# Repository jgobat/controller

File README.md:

# controller

Main control board for simple buoyancy driven underwater vehicles. Based around Teensy 3.6.

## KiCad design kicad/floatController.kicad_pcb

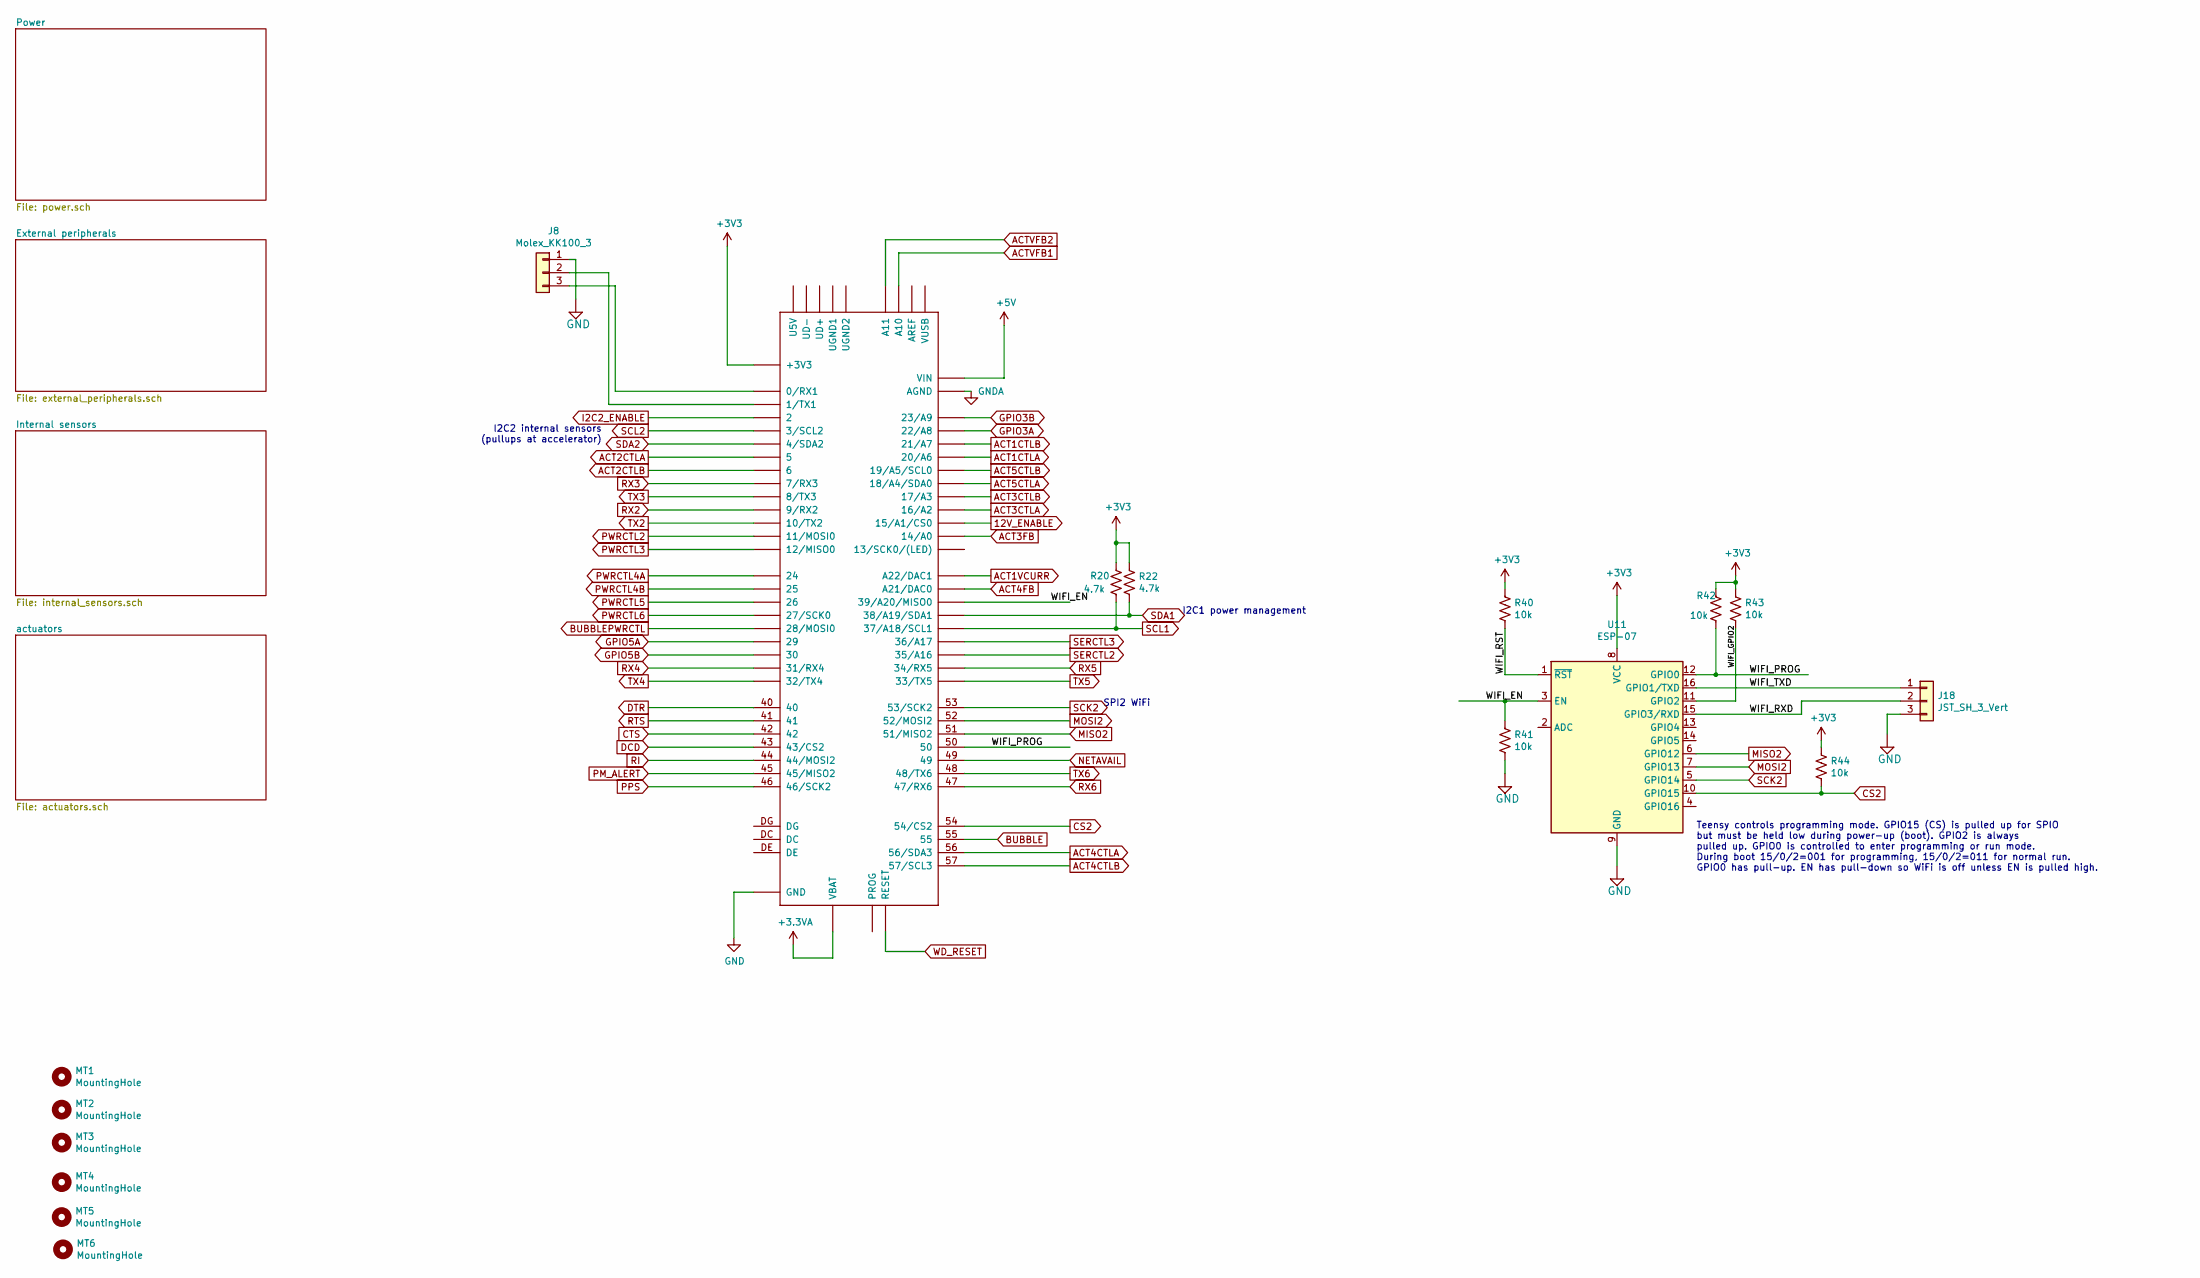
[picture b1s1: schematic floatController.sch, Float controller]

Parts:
J8: Molex_KK100_3; Molex_KK-254_AE-6410-03A_1x03_P2.54mm_Vertical; Manufacturer pn 0022235031; Digikey WM13451-ND
J18: JST_SH_3_Vert; JST_SH_BM03B-SRSS-TB_1x03-1MP_P1.00mm_Vertical; Manufacturer pn BM03B-SRSS-TB(LF)(SN); Digikey 455-1789-1-ND
MT1, MT2, MT3, MT4: MountingHole; MountingHole_3mm_Pad
MT5, MT6: MountingHole; MountingHole_2.5mm
R20, R22: 4.7k; R_0603_1608Metric_Pad1.05x0.95mm_HandSolder; Rating 5%, 1/10W; Manufacturer pn ERJ-3GEYJ472V; Digikey P4.7KGCT-ND
R40, R41, R42, R43, R44: 10k; R_0603_1608Metric_Pad1.05x0.95mm_HandSolder; Manufacturer pn ERJ-3GEYJ103V; Digikey P10KGCT-ND
U1: TEENSY_3.5_3.6; Digikey 1568-1442-ND
U11: ESP-07; Manufacturer pn ESP-07S; Digikey ESP-07S-ND

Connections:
12V_ENABLE: U1.15 (15/A1/CS0); also elsewhere on the board
+3.3VA: U1.VBAT; also elsewhere on the board
+3V3: R20.1, R22.1, R40.1, R42.1, R43.1, R44.1, U1.3V3 (+3V3), U1.3V3_2, U1.3V3_3, U1.3V3_LO, U11.8 (VCC); also elsewhere on the board
+5V: U1.VIN; also elsewhere on the board
/WIFI_EN: R41.1, U1.39 (39/A20/MISO0), U11.3 (EN)
/WIFI_GPIO2: R43.2, U11.11 (GPIO2)
/WIFI_PROG: R42.2, U1.50, U11.12 (GPIO0)
/WIFI_RST: R40.2, U11.1 (~RST)
/WIFI_RXD: J18.2, U11.15 (GPIO3/RXD)
/WIFI_TXD: J18.1, U11.16 (GPIO1/TXD)
ACT1CTLA: U1.20 (20/A6); also elsewhere on the board
ACT1CTLB: U1.21 (21/A7); also elsewhere on the board
ACT1VCURR: U1.A22 (A22/DAC1); also elsewhere on the board
ACT2CTLA: U1.5; also elsewhere on the board
ACT2CTLB: U1.6; also elsewhere on the board
ACT3CTLA: U1.16 (16/A2); also elsewhere on the board
ACT3CTLB: U1.17 (17/A3); also elsewhere on the board
ACT3FB: U1.14 (14/A0); also elsewhere on the board
ACT4CTLA: U1.56 (56/SDA3); also elsewhere on the board
ACT4CTLB: U1.57 (57/SCL3); also elsewhere on the board
ACT4FB: U1.A21 (A21/DAC0); also elsewhere on the board
ACT5CTLA: U1.18 (18/A4/SDA0); also elsewhere on the board
ACT5CTLB: U1.19 (19/A5/SCL0); also elsewhere on the board
ACTVFB1: U1.A10; also elsewhere on the board
ACTVFB2: U1.A11; also elsewhere on the board
BUBBLE: U1.55; also elsewhere on the board
BUBBLEPWRCTL: U1.28 (28/MOSI0); also elsewhere on the board
CS2: R44.2, U1.54 (54/CS2), U11.10 (GPIO15)
CTS: U1.42; also elsewhere on the board
DCD: U1.43 (43/CS2); also elsewhere on the board
DTR: U1.40; also elsewhere on the board
GND: J8.1, J18.3, R41.2, U1.GND, U1.GND2, U1.GND3, U1.GND4, U1.GND5, U11.9 (GND); also elsewhere on the board
GNDA: U1.AGND; also elsewhere on the board
GPIO3A: U1.22 (22/A8); also elsewhere on the board
GPIO3B: U1.23 (23/A9); also elsewhere on the board
GPIO5A: U1.29; also elsewhere on the board
GPIO5B: U1.30; also elsewhere on the board
I2C2_ENABLE: U1.2; also elsewhere on the board
MISO2: U1.51 (51/MISO2), U11.6 (GPIO12)
MOSI2: U1.52 (52/MOSI2), U11.7 (GPIO13)
NETAVAIL: U1.49; also elsewhere on the board
unnamed: J8.2, U1.1 (1/TX1)
unnamed: J8.3, U1.0 (0/RX1)
PM_ALERT: U1.45 (45/MISO2); also elsewhere on the board
PPS: U1.46 (46/SCK2); also elsewhere on the board
PWRCTL2: U1.11 (11/MOSI0); also elsewhere on the board
PWRCTL3: U1.12 (12/MISO0); also elsewhere on the board
PWRCTL4A: U1.24; also elsewhere on the board
PWRCTL4B: U1.25; also elsewhere on the board
PWRCTL5: U1.26; also elsewhere on the board
PWRCTL6: U1.27 (27/SCK0); also elsewhere on the board
RI: U1.44 (44/MOSI2); also elsewhere on the board
RTS: U1.41; also elsewhere on the board
RX2: U1.9 (9/RX2); also elsewhere on the board
RX3: U1.7 (7/RX3); also elsewhere on the board
RX4: U1.31 (31/RX4); also elsewhere on the board
RX5: U1.34 (34/RX5); also elsewhere on the board
RX6: U1.47 (47/RX6); also elsewhere on the board
SCK2: U1.53 (53/SCK2), U11.5 (GPIO14)
SCL1: R20.2, U1.37 (37/A18/SCL1); also elsewhere on the board
SCL2: U1.3 (3/SCL2); also elsewhere on the board
SDA1: R22.2, U1.38 (38/A19/SDA1); also elsewhere on the board
SDA2: U1.4 (4/SDA2); also elsewhere on the board
SERCTL2: U1.35 (35/A16); also elsewhere on the board
SERCTL3: U1.36 (36/A17); also elsewhere on the board
TX2: U1.10 (10/TX2); also elsewhere on the board
TX3: U1.8 (8/TX3); also elsewhere on the board
TX4: U1.32 (32/TX4); also elsewhere on the board
TX5: U1.33 (33/TX5); also elsewhere on the board
TX6: U1.48 (48/TX6); also elsewhere on the board
WD_RESET: U1.RESET; also elsewhere on the board

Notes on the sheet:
I2C1 power management
I2C2 internal sensors (pullups at accelerator)
SPI2 WiFi
Teensy controls programming mode. GPIO15 (CS) is pulled up for SPIO but must be held low during power-up (boot). GPIO2 is always pulled up. GPIO0 is controlled to enter programming or run mode. During boot 15/0/2=001 for programming, 15/0/2=011 for normal run. GPIO0 has pull-up. EN has pull-down so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

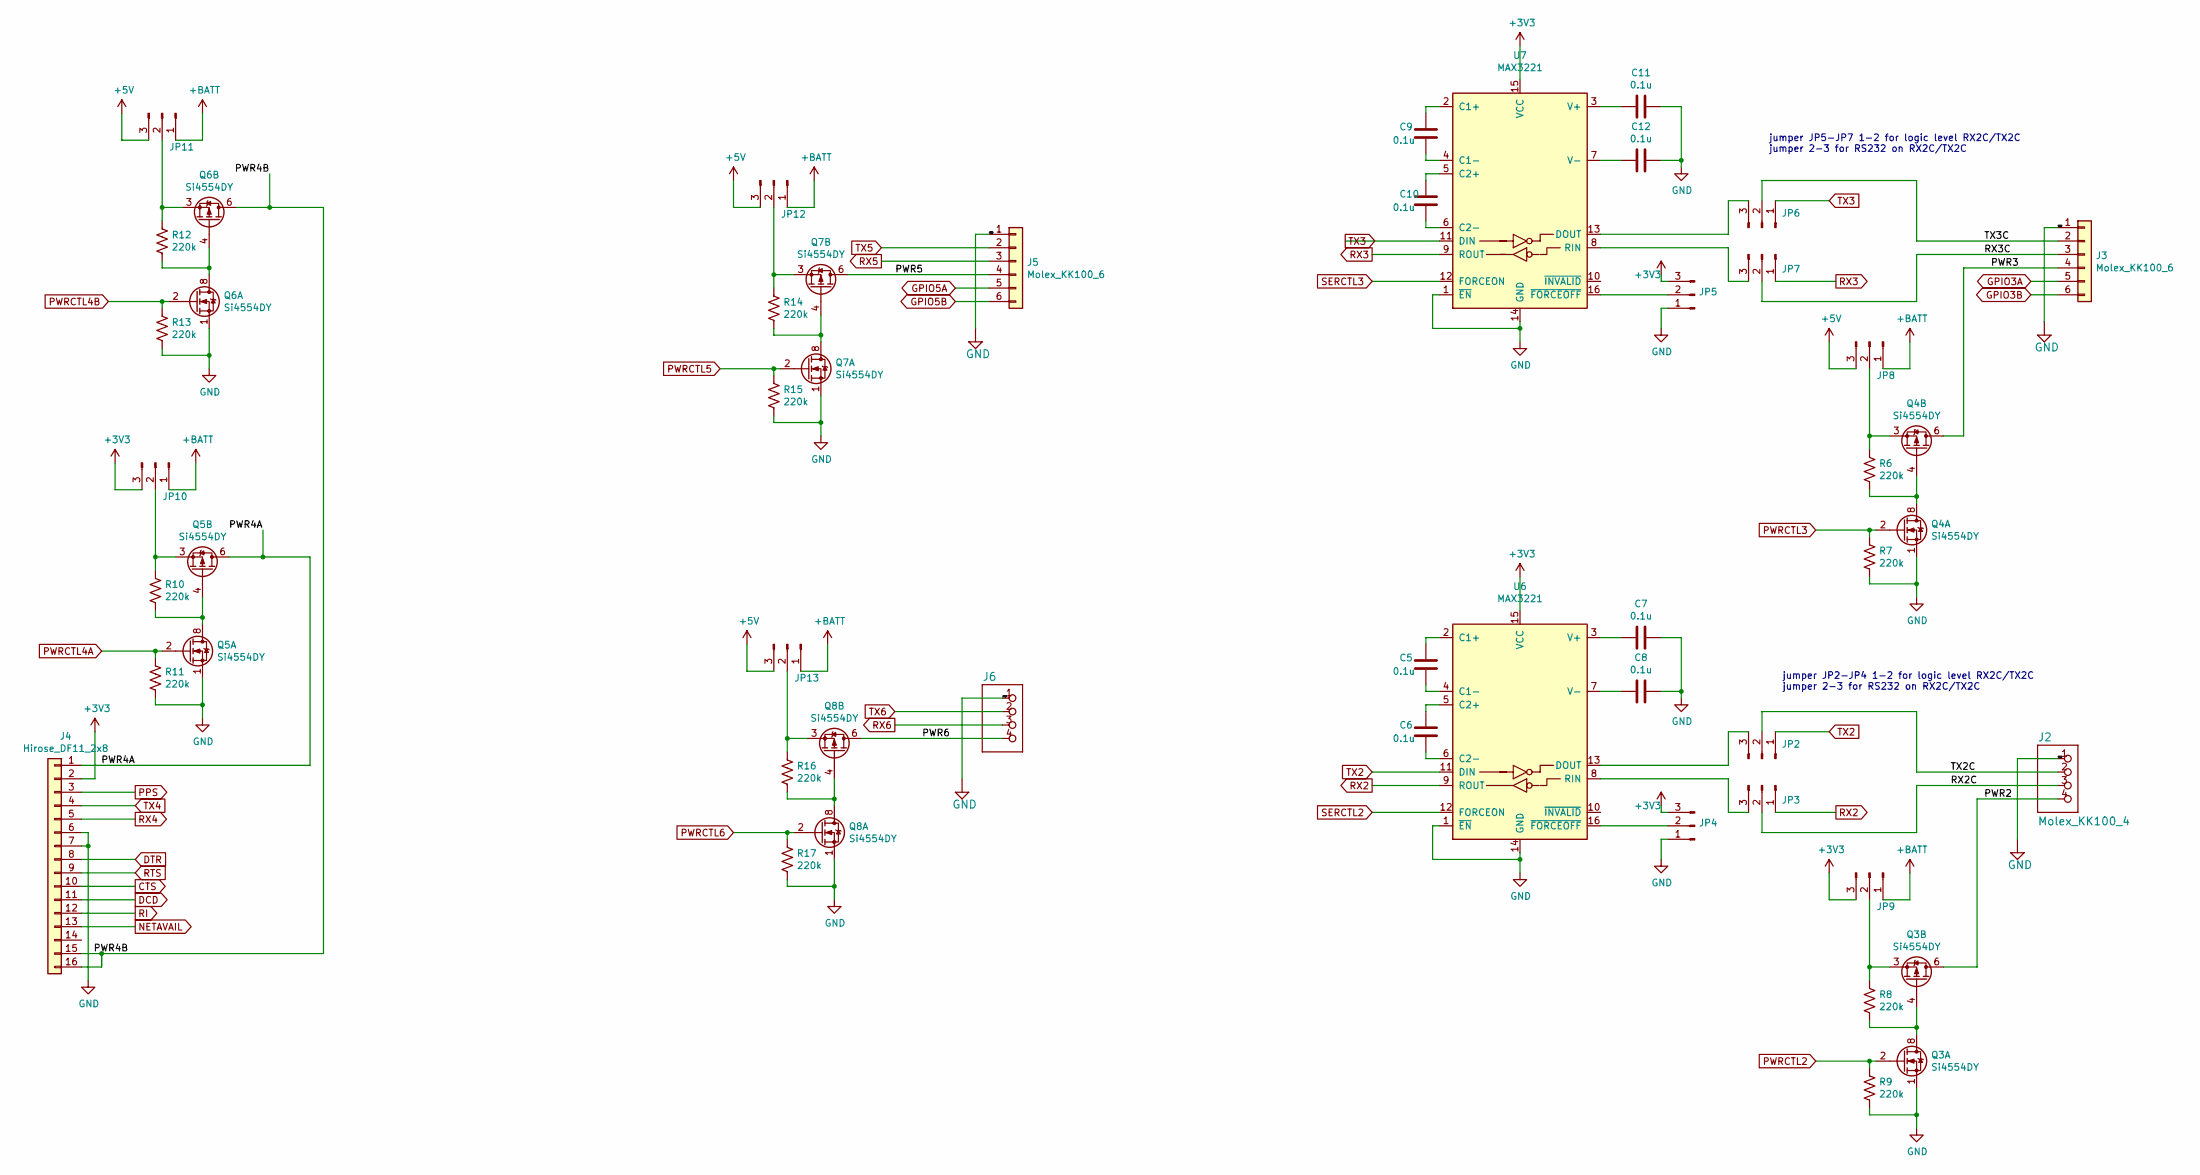
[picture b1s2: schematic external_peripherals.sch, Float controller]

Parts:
C5, C6, C7, C8, C9, C10, C11, C12: 0.1u; C_0603_1608Metric_Pad1.05x0.95mm_HandSolder; Manufacturer pn GCJ188R71E104KA12D‎; Digikey 490-16477-1-ND
J2, J6: Molex_KK100_4; Molex_KK-254_AE-6410-04A_1x04_P2.54mm_Vertical; Manufacturer pn 0022232041; Digikey WM4202-ND
J3, J5: Molex_KK100_6; Molex_KK-254_AE-6410-06A_1x06_P2.54mm_Vertical; Manufacturer pn 0022232061; Digikey WM4204-ND
J4: Hirose_DF11_2x8; Hirose_DF11-16DP-2DSA_2x08_P2.00mm_Vertical; Manufacturer pn DF11-16DP-2DSA(01); Digikey H2856-ND
JP2, JP3, JP4, JP5, JP6, JP7, JP8, JP9, JP12, JP13: PinHead_2.54mm_3; PinHeader_1x03_P2.54mm_Vertical
JP10: 0.003 0603; R0603_3position_jumper; Digikey 738-CSS0603FT3L00CT-ND
JP11: 0.003 0603; R0603_3position_jumper
Q3, Q4, Q5, Q6, Q7, Q8: Si4554DY; SOIC-8_3.9x4.9mm_P1.27mm; Manufacturer pn SI4554DY-T1-GE3; Digikey SI4554DY-T1-GE3CT-ND
R6, R7, R8, R9, R10, R11, R12, R13, R14, R15, R16, R17: 220k; R_0603_1608Metric_Pad1.05x0.95mm_HandSolder; Rating 5%, 1/10W; Manufacturer pn ERJ-3GEYJ224V; Digikey P220KGCT-ND
U6, U7: MAX3221; SSOP-16_5.3x6.2mm_P0.65mm; Manufacturer pn MAX3221IDBR; Digikey 296-9595-1-ND

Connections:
+3V3: J4.2, JP4.3, JP5.3, JP9.3, JP10.3, U6.15 (VCC), U7.15 (VCC); also elsewhere on the board
+5V: JP8.3, JP11.3, JP12.3, JP13.3; also elsewhere on the board
+BATT: JP8.1, JP9.1, JP10.1, JP11.1, JP12.1, JP13.1; also elsewhere on the board
/External peripherals/PWR2: J2.4, Q3.5 (D), Q3.6 (D)
/External peripherals/PWR3: J3.4, Q4.5 (D), Q4.6 (D)
/External peripherals/PWR4A: J4.1, Q5.5 (D), Q5.6 (D)
/External peripherals/PWR4B: J4.15, J4.16, Q6.5 (D), Q6.6 (D)
/External peripherals/PWR5: J5.4, Q7.5 (D), Q7.6 (D)
/External peripherals/PWR6: J6.4, Q8.5 (D), Q8.6 (D)
/External peripherals/RX2C: J2.3, JP3.2
/External peripherals/RX3C: J3.3, JP7.2
/External peripherals/TX2C: J2.2, JP2.2
/External peripherals/TX3C: J3.2, JP6.2
CTS: J4.10; also elsewhere on the board
DCD: J4.11; also elsewhere on the board
DTR: J4.8; also elsewhere on the board
GND: C7.1, C8.1, C11.1, C12.1, J2.1, J3.1, J4.6, J4.7, J5.1, J6.1, JP4.1, JP5.1, Q3.1 (S), Q4.1 (S), Q5.1 (S), Q6.1 (S), Q7.1 (S), Q8.1 (S), R7.2, R9.2, R11.2, R13.2, R15.2, R17.2, U6.1 (~EN), U6.14 (GND), U7.1 (~EN), U7.14 (GND); also elsewhere on the board
GPIO3A: J3.5; also elsewhere on the board
GPIO3B: J3.6; also elsewhere on the board
GPIO5A: J5.5; also elsewhere on the board
GPIO5B: J5.6; also elsewhere on the board
NETAVAIL: J4.13; also elsewhere on the board
unnamed: C5.1, U6.2 (C1+)
unnamed: C5.2, U6.4 (C1-)
unnamed: C6.1, U6.5 (C2+)
unnamed: C6.2, U6.6 (C2-)
unnamed: C7.2, U6.3 (V+)
unnamed: C8.2, U6.7 (V-)
unnamed: C9.1, U7.2 (C1+)
unnamed: C9.2, U7.4 (C1-)
unnamed: C10.1, U7.5 (C2+)
unnamed: C10.2, U7.6 (C2-)
unnamed: C11.2, U7.3 (V+)
unnamed: C12.2, U7.7 (V-)
unnamed: JP2.3, U6.13 (DOUT)
unnamed: JP3.3, U6.8 (RIN)
unnamed: JP4.2, U6.16 (~FORCEOFF)
unnamed: JP5.2, U7.16 (~FORCEOFF)
unnamed: JP6.3, U7.13 (DOUT)
unnamed: JP7.3, U7.8 (RIN)
unnamed: JP8.2, Q4.3 (1), R6.1
unnamed: JP9.2, Q3.3 (1), R8.1
unnamed: JP10.2, Q5.3 (1), R10.1
unnamed: JP11.2, Q6.3 (1), R12.1
unnamed: JP12.2, Q7.3 (1), R14.1
unnamed: JP13.2, Q8.3 (1), R16.1
unnamed: Q3.4 (G), Q3.7 (D), Q3.8 (D), R8.2
unnamed: Q4.4 (G), Q4.7 (D), Q4.8 (D), R6.2
unnamed: Q5.4 (G), Q5.7 (D), Q5.8 (D), R10.2
unnamed: Q6.4 (G), Q6.7 (D), Q6.8 (D), R12.2
unnamed: Q7.4 (G), Q7.7 (D), Q7.8 (D), R14.2
unnamed: Q8.4 (G), Q8.7 (D), Q8.8 (D), R16.2
PPS: J4.3; also elsewhere on the board
PWRCTL2: Q3.2 (G), R9.1; also elsewhere on the board
PWRCTL3: Q4.2 (G), R7.1; also elsewhere on the board
PWRCTL4A: Q5.2 (G), R11.1; also elsewhere on the board
PWRCTL4B: Q6.2 (G), R13.1; also elsewhere on the board
PWRCTL5: Q7.2 (G), R15.1; also elsewhere on the board
PWRCTL6: Q8.2 (G), R17.1; also elsewhere on the board
RI: J4.12; also elsewhere on the board
RTS: J4.9; also elsewhere on the board
RX2: JP3.1, U6.9 (ROUT); also elsewhere on the board
RX3: JP7.1, U7.9 (ROUT); also elsewhere on the board
RX4: J4.5; also elsewhere on the board
RX5: J5.3; also elsewhere on the board
RX6: J6.3; also elsewhere on the board
SERCTL2: U6.12 (FORCEON); also elsewhere on the board
SERCTL3: U7.12 (FORCEON); also elsewhere on the board
TX2: JP2.1, U6.11 (DIN); also elsewhere on the board
TX3: JP6.1, U7.11 (DIN); also elsewhere on the board
TX4: J4.4; also elsewhere on the board
TX5: J5.2; also elsewhere on the board
TX6: J6.2; also elsewhere on the board

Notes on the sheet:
jumper JP5-JP7 1-2 for logic level RX2C/TX2C jumper 2-3 for RS232 on RX2C/TX2C
jumper JP2-JP4 1-2 for logic level RX2C/TX2C jumper 2-3 for RS232 on RX2C/TX2C

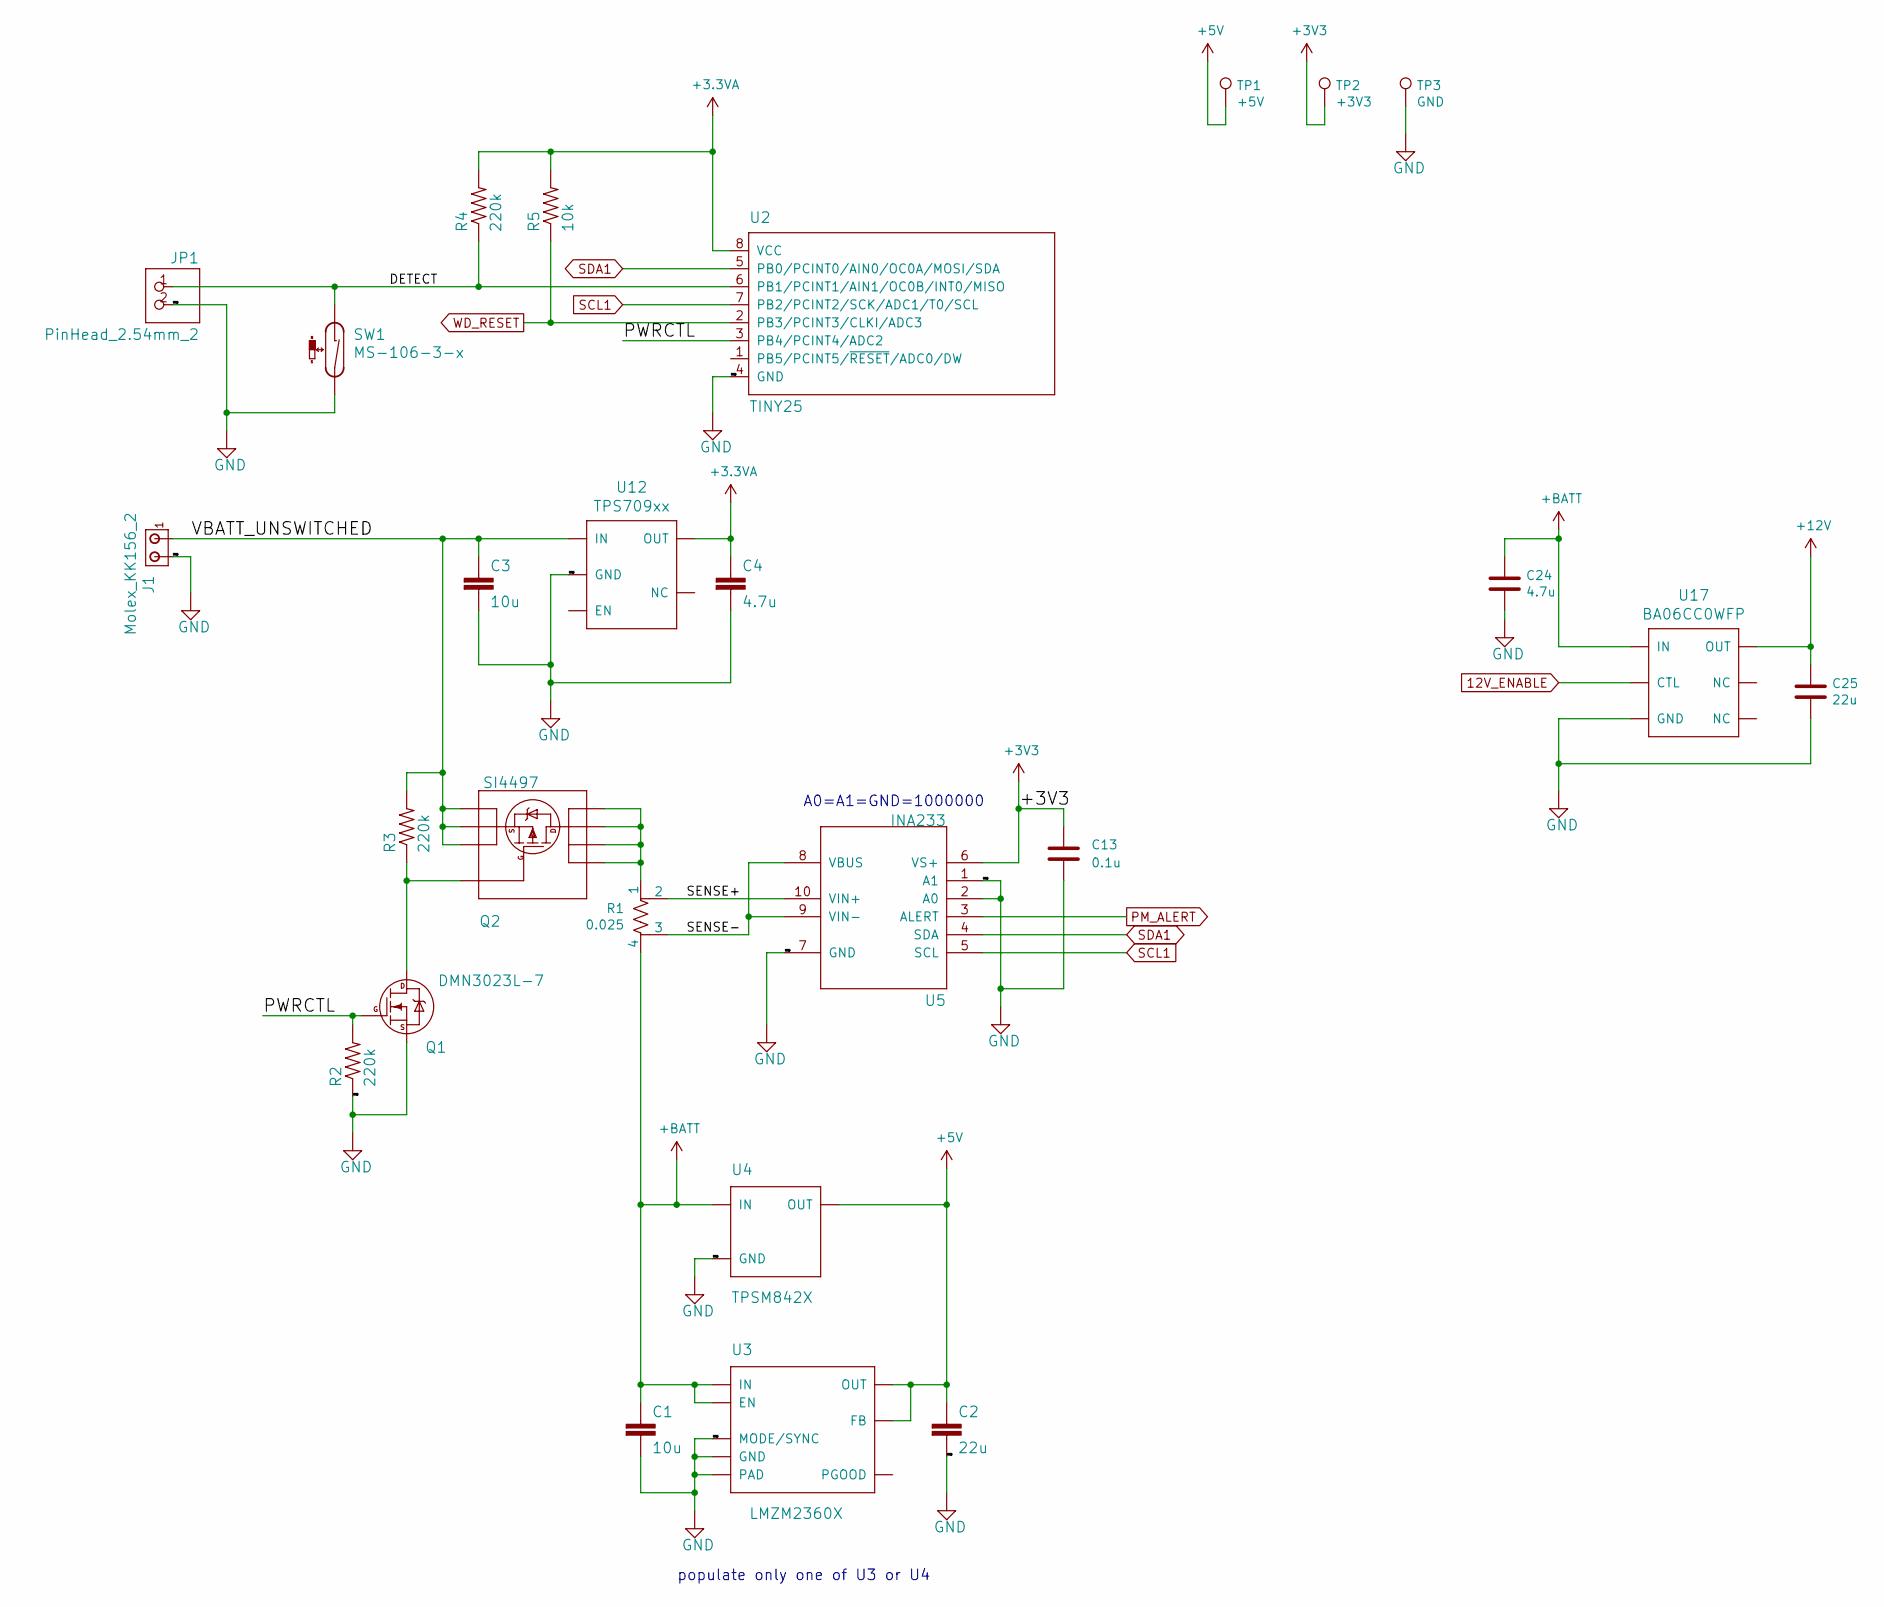
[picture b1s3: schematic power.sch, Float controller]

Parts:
C1: 10u; C_1206_3216Metric_Pad1.42x1.75mm_HandSolder; Rating 7.3u effective at 15V; Manufacturer pn ‎GCM32ER71E106KA57L‎; Digikey 490-4798-1-ND‎
C2: 22u; C_1206_3216Metric_Pad1.42x1.75mm_HandSolder; Rating 20u effective at 5V; Manufacturer pn ‎GCM32ER71A226KE12L‎; Digikey 490-4797-1-ND‎
C3: 10u; C_0805_2012Metric_Pad1.15x1.40mm_HandSolder; Rating 2.2u at 15V; Manufacturer pn GRM21BR6YA106KE43L‎; Digikey 490-10514-1-ND‎
C4: 4.7u; C_0603_1608Metric_Pad1.05x0.95mm_HandSolder; Rating 2.3u at 3.3V (min 1.5u for Vout > 1.5V); Manufacturer pn ‎GRM185R61C475ME11D; Digikey 490-16347-1-ND
C13: 0.1u; C_0603_1608Metric_Pad1.05x0.95mm_HandSolder; Manufacturer pn GCJ188R71E104KA12D‎; Digikey 490-16477-1-ND
C24: 4.7u; C_1206_3216Metric_Pad1.42x1.75mm_HandSolder; Rating 50V
C25: 22u; C_1210_3225Metric_Pad1.42x2.65mm_HandSolder; Rating 25V
J1: Molex_KK156_2; Molex_KK-396_A-41791-0002_1x02_P3.96mm_Vertical; Manufacturer pn ‎0009652028‎; Digikey WM18823-ND
JP1: PinHead_2.54mm_2; PinHeader_1x02_P2.54mm_Vertical
Q1: DMN3023L-7; SOT-23; Manufacturer pn DMN3023L-7; Digikey DMN3023L-7DICT-ND
Q2: SI4497; SOIC-8_3.9x4.9mm_P1.27mm; Manufacturer pn SI4497DY-T1-GE3; Digikey SI4497DY-T1-GE3CT-ND
R1: 0.025; R_Shunt_Ohmite_LVK24; Rating 0.5%, 1W (6A); Manufacturer pn LVK24R025DER; Digikey LVK24R025DERCT-ND
R2, R3, R4: 220k; R_0603_1608Metric_Pad1.05x0.95mm_HandSolder; Rating 5%, 1/10W; Manufacturer pn ERJ-3GEYJ224V; Digikey P220KGCT-ND
R5: 10k; R_0603_1608Metric_Pad1.05x0.95mm_HandSolder; Manufacturer pn ERJ-3GEYJ103V; Digikey P10KGCT-ND
SW1: MS-106-3-x; MK6-6; Rating 10-15AT (others available); Manufacturer pn MS-106-3-1; Digikey 2010-1085-ND
TP1: +5V; TestPoint_Keystone_5000-5004_Miniature; Manufacturer pn 5000; Digikey 36-5000-ND
TP2: +3V3; TestPoint_Keystone_5000-5004_Miniature; Manufacturer pn 5000; Digikey 36-5000-ND
TP3: GND; TestPoint_Keystone_5000-5004_Miniature; Manufacturer pn 5001; Digikey 36-5001-ND
U2: TINY25; DIP-8_W7.62mm_Socket; Rating 20MHz; Manufacturer pn ATTINY25-20PU; Digikey ATTINY25-20PU-ND
U3: LMZM2360X; Rating 4-36V, 1A, 28uA supply; Manufacturer pn LMZM23601V5SILT; Digikey 296-49462-1-ND
U4: TPSM842X; Rating 7-28V, 1.5A,; Manufacturer pn TPSM84205EAB; Digikey 296-47074-ND
U5: INA233; VSSOP-10_3x3mm_P0.5mm; Manufacturer pn INA233AIDGSR; Digikey 296-48136-1-ND
U12: TPS709xx; SOT-23-5; Rating 150mA, 30V max, 2.05uA quiescent; Manufacturer pn TPS70933DBVR; Digikey ‎296-35483-1-ND‎
U17: BA06CC0WFP; TO-252-5_TabPin6; Rating 1A, 25V max, 0uA shutdown; Manufacturer pn BA06CC0WFP-E2; Digikey BA06CC0WFP-E2CT-ND

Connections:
12V_ENABLE: U17.1 (CTL); also elsewhere on the board
+3.3VA: C4.1, R4.2, R5.2, U2.8 (VCC), U12.5 (OUT); also elsewhere on the board
+3V3: C13.1, TP2.1, U5.6 (VS+); also elsewhere on the board
+5V: C2.1, TP1.1, U3.6 (OUT), U3.7 (FB), U4.P$3 (OUT); also elsewhere on the board
+12V: C25.1, U17.4 (OUT); also elsewhere on the board
+BATT: C1.1, C24.1, R1.4, U3.3 (IN), U3.4 (EN), U4.P$1 (IN), U17.2 (IN); also elsewhere on the board
/Power/DETECT: JP1.1, R4.1, SW1.1, U2.6 (PB1/PCINT1/AIN1/OC0B/INT0/MISO)
/Power/PWRCTL: Q1.1 (G), R2.2, U2.3 (PB4/PCINT4/ADC2)
/Power/SENSE+: R1.2, U5.10 (VIN+)
/Power/SENSE-: R1.3, U5.8 (VBUS), U5.9 (VIN-)
/Power/VBATT_UNSWITCHED: C3.1, J1.1, Q2.1 (S@1), Q2.2 (S@2), Q2.3 (S@3), R3.2, U12.1 (IN)
GND: C1.2, C2.2, C3.2, C4.2, C13.2, C24.2, C25.2, J1.2, JP1.2, Q1.2 (S), R2.1, SW1.2, TP3.1, U2.4 (GND), U3.1 (GND), U3.2 (MODE/SYNC), U3.PAD, U4.P$2 (GND), U5.1 (A1), U5.2 (A0), U5.7 (GND), U12.2 (GND), U17.6 (GND); also elsewhere on the board
unnamed: Q1.3 (D), Q2.4 (G), R3.1
unnamed: Q2.5 (D@5), Q2.6 (D@6), Q2.7 (D@7), Q2.8 (D@8), R1.1
PM_ALERT: U5.3 (ALERT); also elsewhere on the board
SCL1: U2.7 (PB2/PCINT2/SCK/ADC1/T0/SCL), U5.5 (SCL); also elsewhere on the board
SDA1: U2.5 (PB0/PCINT0/AIN0/OC0A/MOSI/SDA), U5.4 (SDA); also elsewhere on the board
WD_RESET: R5.1, U2.2 (PB3/PCINT3/CLKI/ADC3); also elsewhere on the board

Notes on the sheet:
populate only one of U3 or U4
A0=A1=GND=1000000

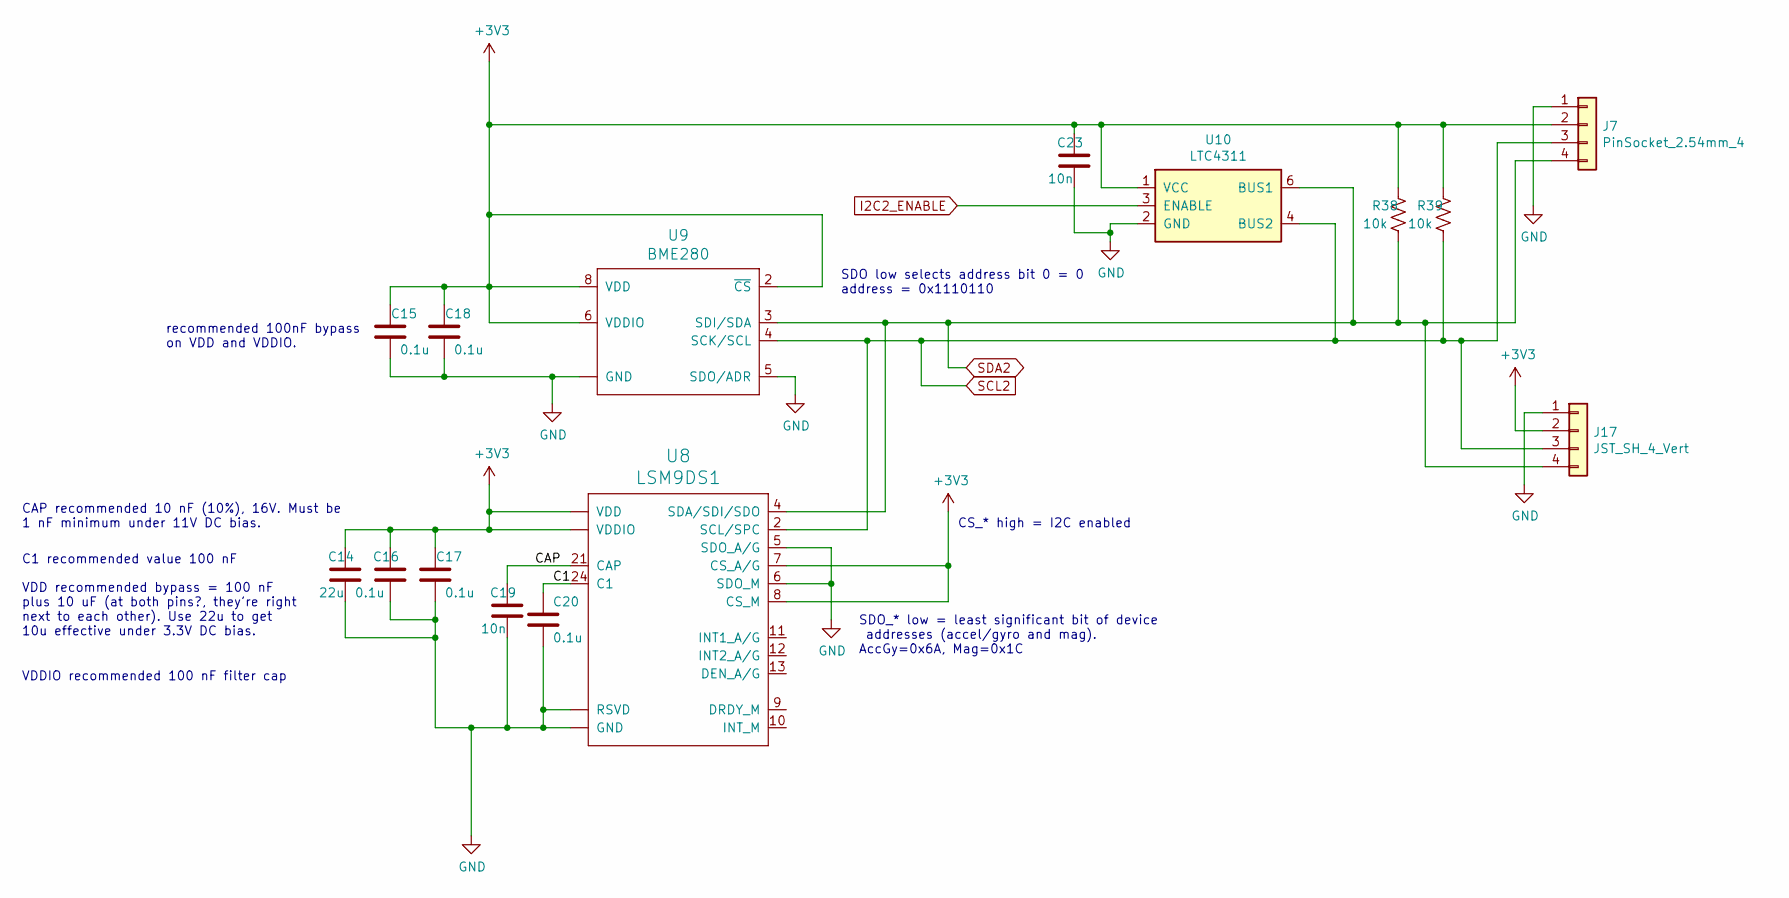
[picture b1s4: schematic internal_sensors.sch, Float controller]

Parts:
C14: 22u; C_0603_1608Metric_Pad1.05x0.95mm_HandSolder; Rating 10V rated, 9u effective at 3.3V; Manufacturer pn GRM187R61A226ME15D; Digikey 490-13243-1-ND
C15, C16, C17, C18, C20: 0.1u; C_0603_1608Metric_Pad1.05x0.95mm_HandSolder; Manufacturer pn GCJ188R71E104KA12D‎; Digikey 490-16477-1-ND
C19, C23: 10n; C_0603_1608Metric_Pad1.05x0.95mm_HandSolder; Manufacturer pn ‎GCM188R72A103KA37J‎; Digikey 490-8028-1-ND
J7: PinSocket_2.54mm_4; PinSocket_1x04_P2.54mm_Vertical
J17: JST_SH_4_Vert; JST_SH_BM04B-SRSS-TB_1x04-1MP_P1.00mm_Vertical; Manufacturer pn BM04B-SRSS-TB(LF)(SN); Digikey 455-1790-1-ND
R38, R39: 10k; R_0603_1608Metric_Pad1.05x0.95mm_HandSolder; Manufacturer pn ERJ-3GEYJ103V; Digikey P10KGCT-ND
U8: LSM9DS1; LGA-24L_3x3.5mm_P0.43mm; Manufacturer pn LSM9DS1TR; Digikey 497-14946-1-ND
U9: BME280; Bosch_LGA-8_2.5x2.5mm_P0.65mm_ClockwisePinNumbering; Manufacturer pn BME280; Digikey 828-1063-1-ND
U10: LTC4311; SOT-363_SC-70-6_Handsoldering; Manufacturer pn LTC4311ISC6#TRMPBF; Digikey LTC4311ISC6#TRMPBFCT-ND

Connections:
+3V3: C14.1, C15.1, C16.1, C17.1, C18.1, C23.1, J7.2, J17.2, R38.1, R39.1, U8.1 (VDDIO), U8.3 (VDDIO), U8.7 (CS_A/G), U8.8 (CS_M), U8.22 (VDD), U8.23 (VDD), U9.2 (~CS), U9.6 (VDDIO), U9.8 (VDD), U10.1 (VCC); also elsewhere on the board
/Internal sensors/C1: C20.1, U8.24 (C1)
/Internal sensors/CAP: C19.1, U8.21 (CAP)
GND: C14.2, C15.2, C16.2, C17.2, C18.2, C19.2, C20.2, C23.2, J7.1, J17.1, U8.5 (SDO_A/G), U8.6 (SDO_M), U8.14 (RSVD), U8.15 (RSVD), U8.16 (RSVD), U8.17 (RSVD), U8.18 (RSVD), U8.19 (GND), U8.20 (GND), U9.1 (GND), U9.5 (SDO/ADR), U9.7 (GND), U10.2 (GND), U10.5 (GND); also elsewhere on the board
I2C2_ENABLE: U10.3 (ENABLE); also elsewhere on the board
SCL2: J7.3, J17.3, R39.2, U8.2 (SCL/SPC), U9.4 (SCK/SCL), U10.4 (BUS2); also elsewhere on the board
SDA2: J7.4, J17.4, R38.2, U8.4 (SDA/SDI/SDO), U9.3 (SDI/SDA), U10.6 (BUS1); also elsewhere on the board

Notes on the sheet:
CS_* high = I2C enabled
SDO_* low = least significant bit of device addresses (accel/gyro and mag). AccGy=0x6A, Mag=0x1C
CAP recommended 10 nF (10%), 16V. Must be 1 nF minimum under 11V DC bias.
C1 recommended value 100 nF
VDD recommended bypass = 100 nF plus 10 uF (at both pins?, they're right next to each other). Use 22u to get 10u effective under 3.3V DC bias.
VDDIO recommended 100 nF filter cap
recommended 100nF bypass on VDD and VDDIO.
SDO low selects address bit 0 = 0 address = 0x1110110
